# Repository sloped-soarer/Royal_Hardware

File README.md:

# Royal_Hardware
Things I have designed and made for the multiplex royal evo / pro.

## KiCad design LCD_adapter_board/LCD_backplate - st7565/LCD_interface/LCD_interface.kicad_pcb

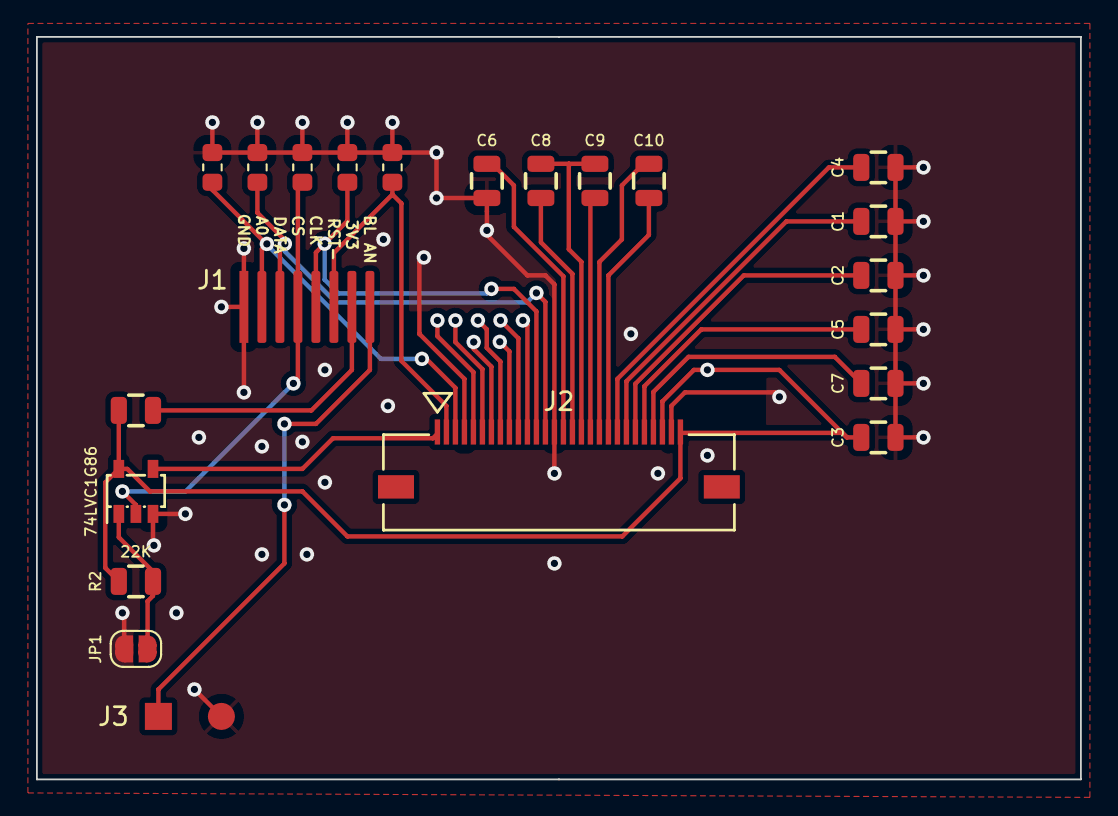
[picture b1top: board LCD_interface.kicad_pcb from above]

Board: 2 copper layers, 58.0 x 41.2 mm, 22 parts (0 on the bottom side), 22 nets.

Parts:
C1, C2, C3, C4, C5, C6, C7, C8, C9, C10: 1UF 25V; C_SM_0805_2012Metric
C11, C12, C13, C14, C15: emc; C_0603_1608Metric_Pad1.0x1.1mm_HandSolder
J1: Conn_01x08_Female; solder_pads_8x4mmx0.5mm_p1.0mm
J2: Conn_01x28; CON_5051102891_MOL
J3: Conn_01x02_Female; solder_pads_2x4mmx0.5mm_p1.0mm
JP1: SolderJumper_2_Open; SolderJumper-2_P1.3mm_Open_RoundedPad1.0x1.5mm
R1: 0; R_SM_0805_2012Metric
R2: 22K; R_SM_0805_2012Metric
U1: 74LVC1G86; SOT-23-5

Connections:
3V3: J1.7, R1.1
/~chip_select: J2.1, U1.4
A0: C15.1, J1.2, J2.3
CLK: C12.1, J1.5, J2.12
DATA: C14.1, J1.3, J2.13
GND: C1.1, C2.2, C3.1, C4.1, C5.2, C6.1, C7.2, C11.2, C12.2, C13.2, C14.2, C15.2, J1.1, J2.4, J2.14, J2.27, J3.2, JP1.1 (A), U1.3 (GND)
unnamed: C1.2, J2.22
unnamed: C2.1, J2.23
unnamed: C4.2, J2.21
unnamed: C5.1, J2.24
unnamed: C6.2, J2.15
unnamed: C7.1, J2.25
unnamed: C8.1, C9.1, J2.17
unnamed: C8.2, J2.16
unnamed: C9.2, J2.18
unnamed: C10.1, J2.19
unnamed: C10.2, J2.20
unnamed: JP1.2 (B), R2.1, U1.1
VCC: C3.2, J2.26, J2.28, R1.2, R2.2, U1.5 (VCC)
backlight_anode: J1.8, J3.1
chip_select: C13.1, J1.4, U1.2
~reset: C11.1, J1.6, J2.2

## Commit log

2025-04-04 Add Gimbal Adapter.
2025-04-04 LCD Adapter design files added. KiCAD V6
